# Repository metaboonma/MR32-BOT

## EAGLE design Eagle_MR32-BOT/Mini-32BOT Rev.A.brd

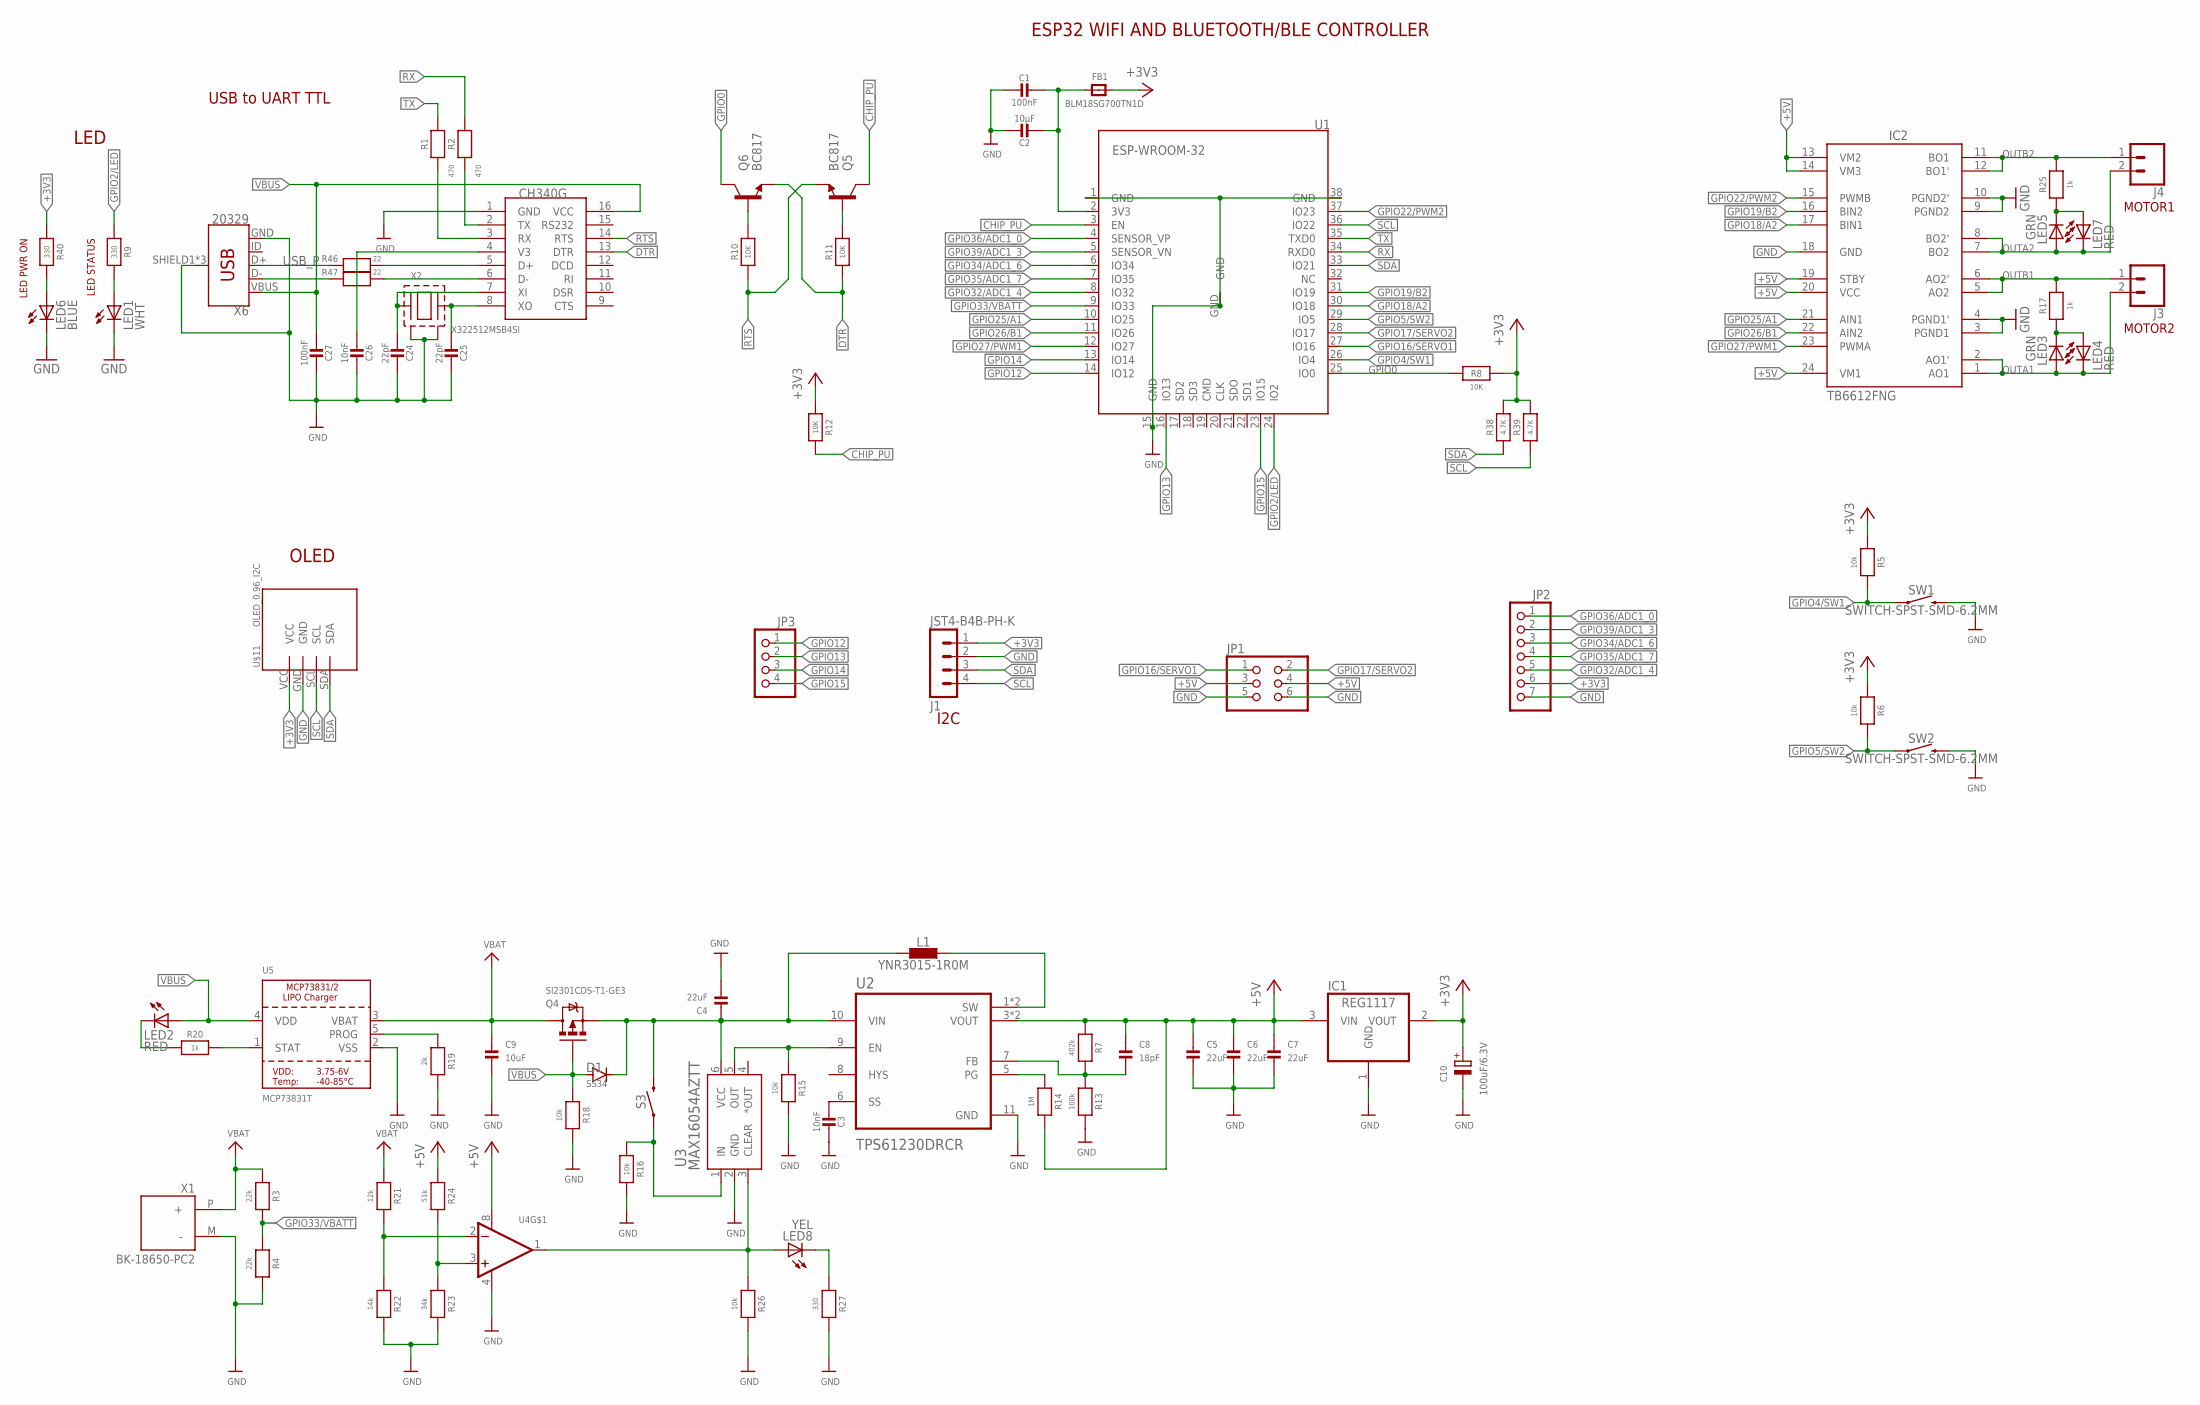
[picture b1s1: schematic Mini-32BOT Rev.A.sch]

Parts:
C1, C27: 100nF; 0603
C2: 10µF; 0805
C3, C26: 10nF; 0603
C4, C5, C6, C7: 22uF; 0805
C8: 18pF; 0603
C9: 10uF; 0805
C10: 100uF/6.3V; CT3528
C24, C25: 22pF; 0603
D1: SS34; DO-214AC
FB1: BLM18SG700TN1D; _0603
IC1: REG1117; SOT223
IC2: TB6612FNG; SSOP24
J1: JST4-B4B-PH-K; JST_B4B-PH-K
J3, J4: CONN_023.5MM; SCREWTERMINAL-3.5MM-2
JP1: PINHD-2X03_2.54; 2X03
JP2: PINHD-1X07_2.54-S; 1X07-S
JP3: PINHD-1X04_2.54-S; 1X04-S
L1: YNR3015-1R0M; L_NR40XX
LED1: WHT; CHIP-LED0805
LED2, LED4, LED7: RED; CHIP-LED0805
LED3, LED5: GRN; CHIP-LED0805
LED6: BLUE; CHIP-LED0805
LED8: YEL; CHIP-LED0805
Q4: SI2301CDS-T1-GE3; SOT23-3
Q5, Q6: BC817; SOT23-3
R1, R2: 470; 0603
R3, R4: 22k; 0603
R5, R6, R15, R16, R18, R26: 10k; 0603
R7: 402k; 0603
R8, R10, R11, R12: 10K; 0603
R9, R27, R40: 330; 0603
R13: 100k; 0603
R14: 1M; 0603
R17, R20, R25: 1k; 0603
R19: 2k; 0603
R21: 12k; 0603
R22: 14k; 0603
R23: 34k; 0603
R24: 51k; 0603
R38, R39: 4.7K; 0603
R46, R47: 22; 0603
S3: MOMENTARY-SWITCH-SPST-PTH-RIGHT-ANGLE-KIT; TACTILE_SWITCH_PTH_RIGHT_ANGLE_KIT
SW1, SW2: SWITCH-SPST-SMD-6.2MM; TACTILE_SWITCH_SMD_6.2MM_TALL
U1: ESP-WROOM-32
U2: TPS61230DRCR; SON50P300X300X100-11N
U3: MAX16054AZTT; 21-0114C
U4: LM358; SOIC8_150MIL
U5: MCP73831T; SOT23-5
U$11: OLED_0.96_I2C
U$24: CH340G; SOIC16
X1: BK-18650-PC2; MPD_BK-18650-PC2
X2: X322512MSB4SI; X3225_4P
X6: 20329; USB-B-MICRO-SMD

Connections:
3V3: C1.1, C2.2, FB1.1, U1.2 (3V3)
+3V3: C10.+, FB1.2, IC1.2 (VOUT), J1.1, JP2.6, R5.1, R6.1, R8.2, R12.1, R38.2, R39.2, R40.1, U$11.VCC
+5V: C5.1, C6.1, C7.1, C8.1, IC1.3 (VIN), IC2.13 (VM2), IC2.14 (VM3), IC2.19 (STBY), IC2.20 (VCC), IC2.24 (VM1), JP1.3, JP1.4, R7.1, R14.2, R24.1, U2.3 (VOUT), U2.4 (VOUT), U4.8 (V+)
CHIP_PU: Q5.3 (C), R12.2, U1.3 (EN)
DTR: Q6.2 (E), R11.1, U$24.13 (DTR)
GND: C1.2, C2.1, C3.1, C4.2, C5.2, C6.2, C7.2, C9.2, C10.-, C24.1, C25.1, C26.1, C27.1, IC1.1 (GND), IC2.3 (PGND1), IC2.4 (PGND1'), IC2.9 (PGND2), IC2.10 (PGND2'), IC2.18 (GND), J1.2, JP1.5, JP1.6, JP2.7, LED1.C, LED6.C, R4.2, R13.2, R15.2, R16.2, R18.2, R19.2, R22.2, R23.2, R26.2, R27.2, SW1.B2 (2), SW2.B2 (2), U1.1 (GND), U1.15 (GND), U1.38 (GND), U1.GND, U2.11 (GND), U3.2 (GND), U4.4 (V-), U5.2 (VSS), U$11.GND, U$24.1 (GND), X1.M (-), X2.P$2 (GND1), X2.P$4 (GND2), X6.GND, X6.SHIELD1 (SHIELD), X6.SHIELD2 (SHIELD), X6.SHIELD3 (SHIELD)
GPIO0: Q6.3 (C), R8.1, U1.25 (IO0)
GPIO2/LED: R9.1, U1.24 (IO2)
GPIO4/SW1: R5.2, SW1.A2 (1), U1.26 (IO4)
GPIO5/SW2: R6.2, SW2.A2 (1), U1.29 (IO5)
GPIO12: JP3.1, U1.14 (IO12)
GPIO13: JP3.2, U1.16 (IO13)
GPIO14: JP3.3, U1.13 (IO14)
GPIO15: JP3.4, U1.23 (IO15)
GPIO16/SERVO1: JP1.1, U1.27 (IO16)
GPIO17/SERVO2: JP1.2, U1.28 (IO17)
GPIO18/A2: IC2.17 (BIN1), U1.30 (IO18)
GPIO19/B2: IC2.16 (BIN2), U1.31 (IO19)
GPIO22/PWM2: IC2.15 (PWMB), U1.37 (IO23)
GPIO25/A1: IC2.21 (AIN1), U1.10 (IO25)
GPIO26/B1: IC2.22 (AIN2), U1.11 (IO26)
GPIO27/PWM1: IC2.23 (PWMA), U1.12 (IO27)
GPIO32/ADC1_4: JP2.5, U1.8 (IO32)
GPIO33/VBATT: R3.2, R4.1, U1.9 (IO33)
GPIO34/ADC1_6: JP2.3, U1.6 (IO34)
GPIO35/ADC1_7: JP2.4, U1.7 (IO35)
GPIO36/ADC1_0: JP2.1, U1.4 (SENSOR_VP)
GPIO39/ADC1_3: JP2.2, U1.5 (SENSOR_VN)
unnamed: C4.1, D1.C, L1.1, Q4.2 (S), S3.2, U2.10 (VIN), U3.6 (VCC)
unnamed: C3.2, U2.6 (SS)
unnamed: L1.2, U2.1 (SW), U2.2 (SW)
unnamed: R15.1, U2.9 (EN), U3.5 (OUT)
unnamed: C8.2, R7.2, R13.1, U2.7 (FB)
unnamed: R14.1, U2.5 (PG)
unnamed: R16.1, S3.1, U3.1 (IN)
unnamed: R21.2, R22.1, U4.2 (-IN)
unnamed: R23.1, R24.2, U4.3 (+IN)
unnamed: LED8.A, R26.1, U3.3 (CLEAR), U4.1 (OUT)
unnamed: LED3.C, LED4.A, R17.1
unnamed: LED5.C, LED7.A, R25.1
unnamed: R19.1, U5.5 (PROG)
unnamed: C25.2, U$24.8 (XO), X2.P$3
unnamed: LED2.C, R20.1
unnamed: R20.2, U5.1 (STAT)
unnamed: C24.2, U$24.7 (XI), X2.P$1
unnamed: LED8.C, R27.1
unnamed: LED1.A, R9.2
unnamed: LED6.A, R40.2
unnamed: Q5.1 (B), R11.2
unnamed: C26.2, U$24.4 (V3)
unnamed: Q6.1 (B), R10.2
unnamed: R2.1, U$24.2 (TX)
unnamed: R1.1, U$24.3 (RX)
unnamed: R46.1, U$24.5 (D+)
unnamed: R47.1, U$24.6 (D-)
OUTA1: IC2.1 (AO1), IC2.2 (AO1'), J3.2, LED3.A, LED4.C
OUTA2: IC2.7 (BO2), IC2.8 (BO2'), J4.2, LED5.A, LED7.C
OUTB1: IC2.5 (AO2), IC2.6 (AO2'), J3.1, R17.2
OUTB2: IC2.11 (BO1), IC2.12 (BO1'), J4.1, R25.2
RTS: Q5.2 (E), R10.1, U$24.14 (RTS)
RX: R2.2, U1.34 (RXD0)
SCL: J1.4, R39.1, U1.36 (IO22), U$11.SCL
SDA: J1.3, R38.1, U1.33 (IO21), U$11.SDA
TX: R1.2, U1.35 (TXD0)
USB_N: R47.2, X6.D-
USB_P: R46.2, X6.D+
VBAT: C9.1, Q4.3 (D), R3.1, R21.1, U5.3 (VBAT), X1.P (+)
VBUS: C27.2, D1.A, LED2.A, Q4.1 (G), R18.1, U5.4 (VDD), U$24.16 (VCC), X6.VBUS

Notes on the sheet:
ESP32 WIFI AND BLUETOOTH/BLE CONTROLLER
LED PWR ON
LED STATUS
LED
MOTOR2
MOTOR1
USB to UART TTL
I2C
OLED

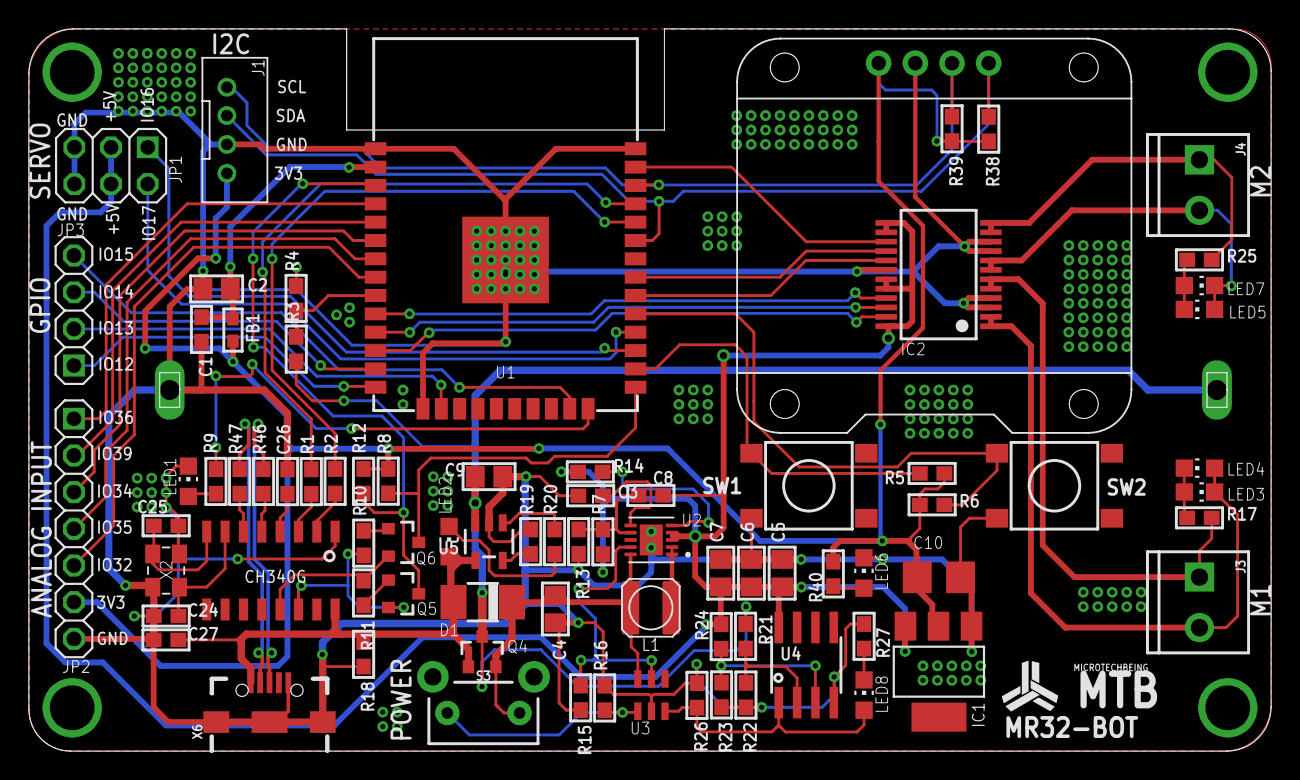
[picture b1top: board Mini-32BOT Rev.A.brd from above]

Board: 2 copper layers, 86.0 x 50.0 mm, 81 parts (1 on the bottom side), 68 nets.

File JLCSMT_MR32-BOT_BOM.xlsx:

Comment | Designator | Footprint | LCSC Part #（optional）
LM358DR | U4 | SOIC8_150MIL | C7950
100k | R13 | 0603_R | C25803
100nF | C1, C27 | 0603_C | C14663
100uF/6.3V | C10 | CT3528 | C16133
10K | R8, R10, R11, R12, R5, R6, R15, R16, R18, R26 | 0603_R | C25804
10nF | C3, C26 | 0603_C | C57112
10uF | C2, C9 | 0805_C | C15850
12k | R21 | 0603_R | C22790
14k | R22 | 0603_R | C22803
18pF | C8 | 0603_C | C1647
1M | R14 | 0603_R | C22935
1k | R17, R20, R25 | 0603_R | C21190
20329 | X6 | USB-B-MICRO-SMD | C40942
22 | R46, R47 | 0603_R | C23345
22k | R3, R4 | 0603_R | C31850
22pF | C24, C25 | 0603_C | C1653
22uF | C4, C5, C6, C7 | 0805_C | C45783
2k | R19 | 0603_R | C22975
330 | R9, R27, R40 | 0603_R | C23138
34k | R23 | 0603_R | C23008
4.7K | R38, R39 | 0603_R | C23162
402k | R7 | 0603_R | C23162
470 | R1, R2 | 0603_R | C23179
51k | R24 | 0603_R | C23196
BC817 | Q5, Q6 | SOT23-3 | C118725
BLM18SG700TN1D | FB1 | _0603 | C85831
BLUE | LED6 | CHIP-LED0805 | C2293
CH340G | U$24 | SOIC16 | C14267
ESP-WROOM-32 | U1 | ESP-WROOM-32 | C95209
GRN | LED3, LED5 | CHIP-LED0805 | C2297
MAX16054AZTT | U3 | 21-0114C | C79401
MCP73831T | U5 | SOT23-5 | C14879
RED | LED2, LED4, LED7 | CHIP-LED0805 | C84256
REG1117 | IC1 | SOT223 | C6186
SI2301CDS-T1-GE3 | Q4 | SOT23-3 | C10487
SS34 | D1 | DO-214AC | C8678
TB6612FNG | IC2 | SSOP24 | C141517
TPS61230DRCR | U2 | SON50P300X300X100-11N | C139626
WHT | LED1 | CHIP-LED0805 | C34499
X322512MSB4SI | X2 | X3225_4P | C9002
YEL | LED8 | CHIP-LED0805 | C2296
YNR3015-1R0M | L1 | L_NR40XX | C340357

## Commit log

2020-05-31 Create new project
2020-08-07 Add example
2020-08-07 Add PPT
2020-08-14 Edit PPT and KB Example
2020-08-14 add pdf 4slide in 1 paper

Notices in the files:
parts and their libraries:
microbuilder: This work is placed in the public domain, and may be freely used for commercial and non-commercial work with the following conditions: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
SparkFun-Retired: Licensing: Creative Commons ShareAlike 4.0 International - https://creativecommons.org/licenses/by-sa/4.0
